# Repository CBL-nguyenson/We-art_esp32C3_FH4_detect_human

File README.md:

# Arduino_Project_Template
      WiFi.begin(network.wifiData.ssid,network.wifiData.pwd);  
      network.wifiData.ssid 
      192.168.4.1

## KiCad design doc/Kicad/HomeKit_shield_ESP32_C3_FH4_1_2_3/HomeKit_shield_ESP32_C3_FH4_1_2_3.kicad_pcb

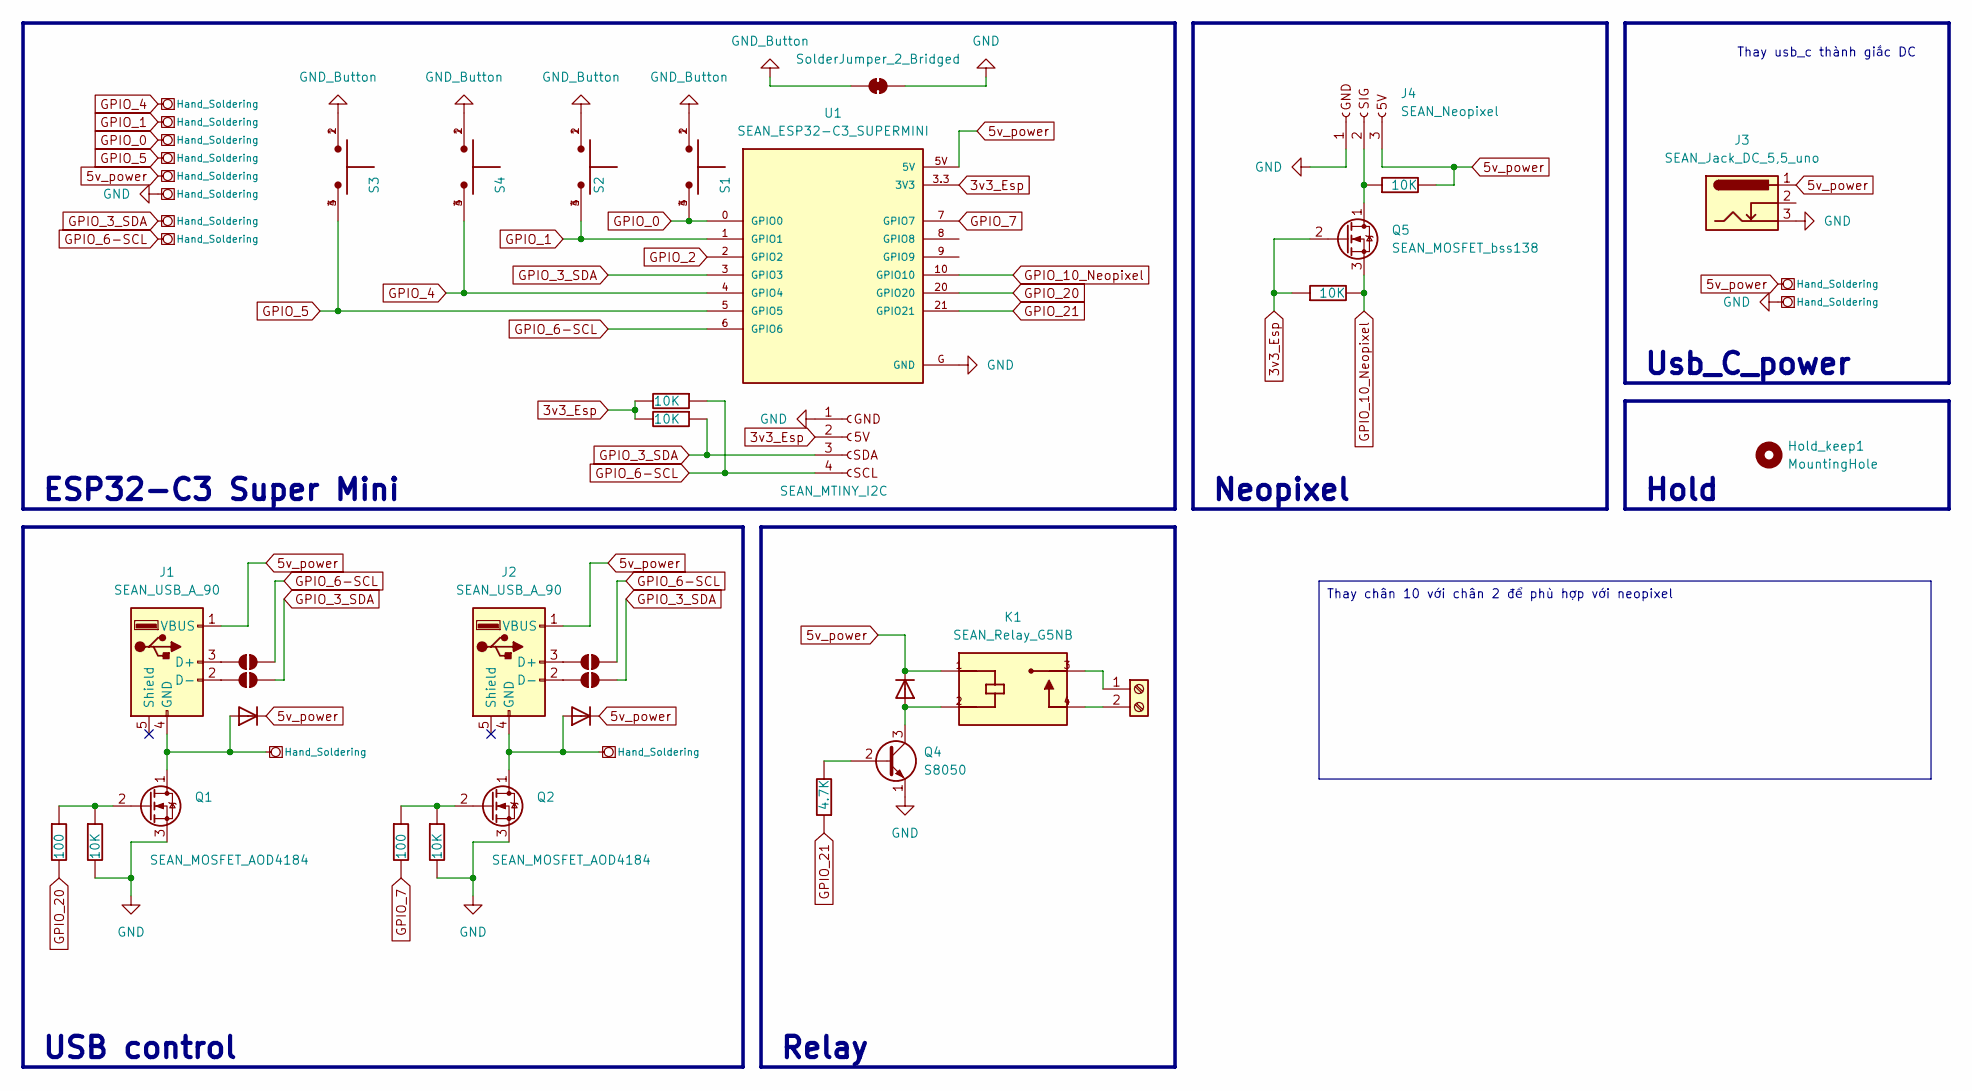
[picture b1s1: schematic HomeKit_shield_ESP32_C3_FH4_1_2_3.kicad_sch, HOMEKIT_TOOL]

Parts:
D1, D2, D3: SEAN_D; SEAN_Diode_1N4007
Hold_keep1: MountingHole; SEAN_MountingHole_3mm_isolated
J1, J2: SEAN_USB_A_90
J3: SEAN_Jack_DC_5,5_uno; SEAN_Jack_DC_5,5_uno_
J4: SEAN_Neopixel
J5: SEAN_MTINY_I2C; SEAN_Mtiny_I2C
JP1, JP2, JP3, JP4: SolderJumper_2_Open; SolderJumper-2_P1.3mm_Open_TrianglePad1.0x1.5mm
JP5: SolderJumper_2_Bridged; SolderJumper-2_P1.3mm_Bridged_RoundedPad1.0x1.5mm
K1: SEAN_Relay_G5NB; SEAN_RELAY_HF46F; PARTREV 1.00
Q1, Q2: SEAN_MOSFET_AOD4184
Q4: S8050; SOT-23-3
Q5: SEAN_MOSFET_bss138
R1, R2, R6, R7, R9, R11: 10K; R_0603_1608Metric_Pad0.98x0.95mm_HandSolder
R3: 4.7K; R_0603_1608Metric_Pad0.98x0.95mm_HandSolder
R4, R5: 100; R_0603_1608Metric_Pad0.98x0.95mm_HandSolder
S1, S2, S3, S4: SEAN_Button_4.2x3.3_SMD_V1
SEAN_Mtiny_Terminal_3.81: SEAN_Mtiny_Terminal_3.81
U1: SEAN_ESP32-C3_SUPERMINI
U2, U3, U4, U5, U6, U7, U8, U9, U10, U11, U12, U13: SEAN_Hand_Solderring

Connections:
3v3_Esp: J5.2 (5V), Q5.2 (G), R6.1, R7.2, R11.2, U1.3.3 (3V3)
5v_power: D1.1 (K), D2.1 (K), D3.1 (K), J1.1 (VBUS), J2.1 (VBUS), J3.1, J4.3 (SDA), K1.1, R9.2, U1.5V, U3.1 (Hand_Soldering), U5.1 (Hand_Soldering)
GND: J3.3, J4.1 (GND), J5.1 (GND), JP5.2 (B), Q1.3 (S), Q2.3 (S), Q4.1 (E), R1.2, R2.2, U1.G (GND), U8.1 (Hand_Soldering), U13.1 (Hand_Soldering)
GND_Button: JP5.1 (A), S1.1, S1.2, S2.1, S2.2, S3.1, S3.2, S4.1, S4.2
GPIO_0: S1.3, S1.4, U1.0 (GPIO0), U6.1 (Hand_Soldering)
GPIO_1: S2.3, S2.4, U1.1 (GPIO1), U7.1 (Hand_Soldering)
GPIO_2: U1.2 (GPIO2)
GPIO_3_SDA: J5.3 (SDA), JP2.2 (B), JP3.2 (B), R7.1, U1.3 (GPIO3), U11.1 (Hand_Soldering)
GPIO_4: S4.3, S4.4, U1.4 (GPIO4), U2.1 (Hand_Soldering)
GPIO_5: S3.3, S3.4, U1.5 (GPIO5), U4.1 (Hand_Soldering)
GPIO_6-SCL: J5.4 (SCL), JP1.2 (B), JP4.2 (B), R11.1, U1.6 (GPIO6), U12.1 (Hand_Soldering)
GPIO_7: R5.2, U1.7 (GPIO7)
GPIO_10_Neopixel: Q5.3 (S), R6.2, U1.10 (GPIO10)
GPIO_20: R4.2, U1.20 (GPIO20)
GPIO_21: R3.1, U1.21 (GPIO21)
unnamed: D1.2 (A), J1.4 (GND), Q1.1 (D), U10.1 (Hand_Soldering)
unnamed: D2.2 (A), J2.4 (GND), Q2.1 (D), U9.1 (Hand_Soldering)
unnamed: D3.2 (A), K1.2, Q4.3 (C)
unnamed: J1.3 (D+), JP4.1 (A)
unnamed: J1.2 (D-), JP3.1 (A)
unnamed: J2.3 (D+), JP1.1 (A)
unnamed: J2.2 (D-), JP2.1 (A)
unnamed: J4.2 (5V), Q5.1 (D), R9.1
unnamed: Q1.2 (G), R1.1, R4.1
unnamed: Q2.2 (G), R2.1, R5.1
unnamed: Q4.2 (B), R3.2
unnamed: K1.3, SEAN_Mtiny_Terminal_3.81.1
unnamed: K1.4, SEAN_Mtiny_Terminal_3.81.2

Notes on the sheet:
Thay chân 10 với chân 2 để phù hợp với neopixel
Relay
ESP32-C3 Super Mini
Thay usb_c thành giắc DC
Hold
Usb_C_power
Neopixel
USB control

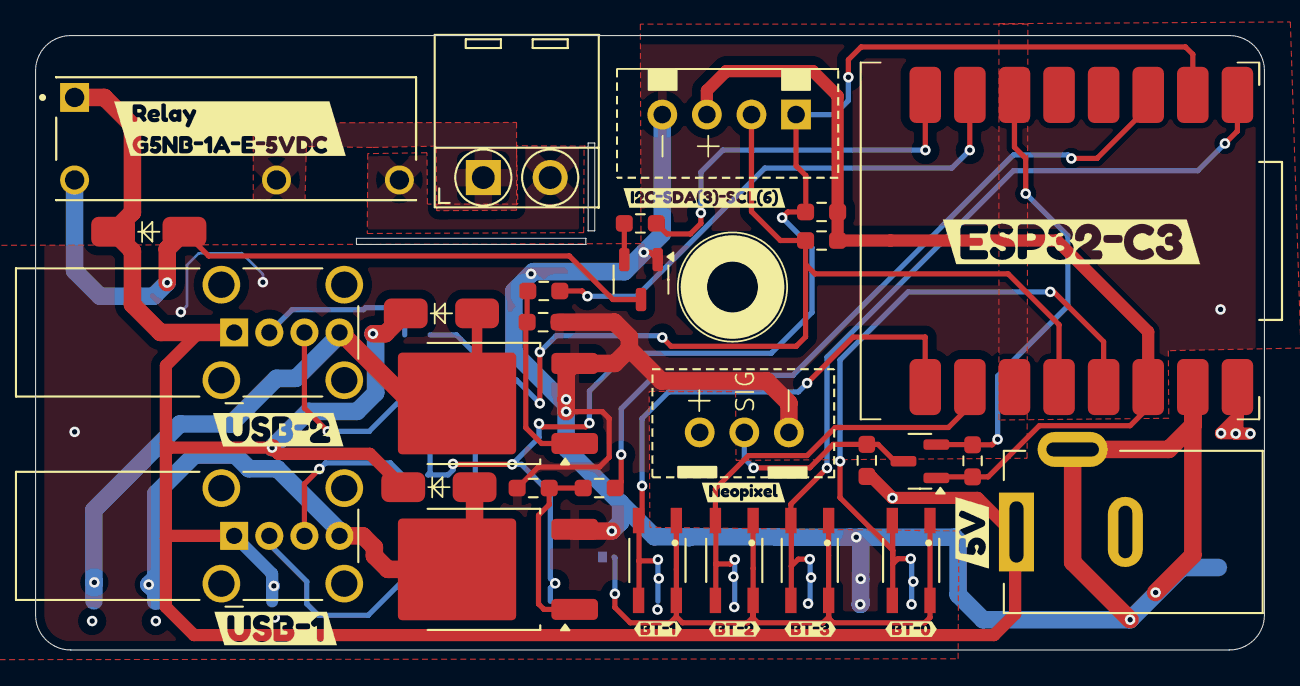
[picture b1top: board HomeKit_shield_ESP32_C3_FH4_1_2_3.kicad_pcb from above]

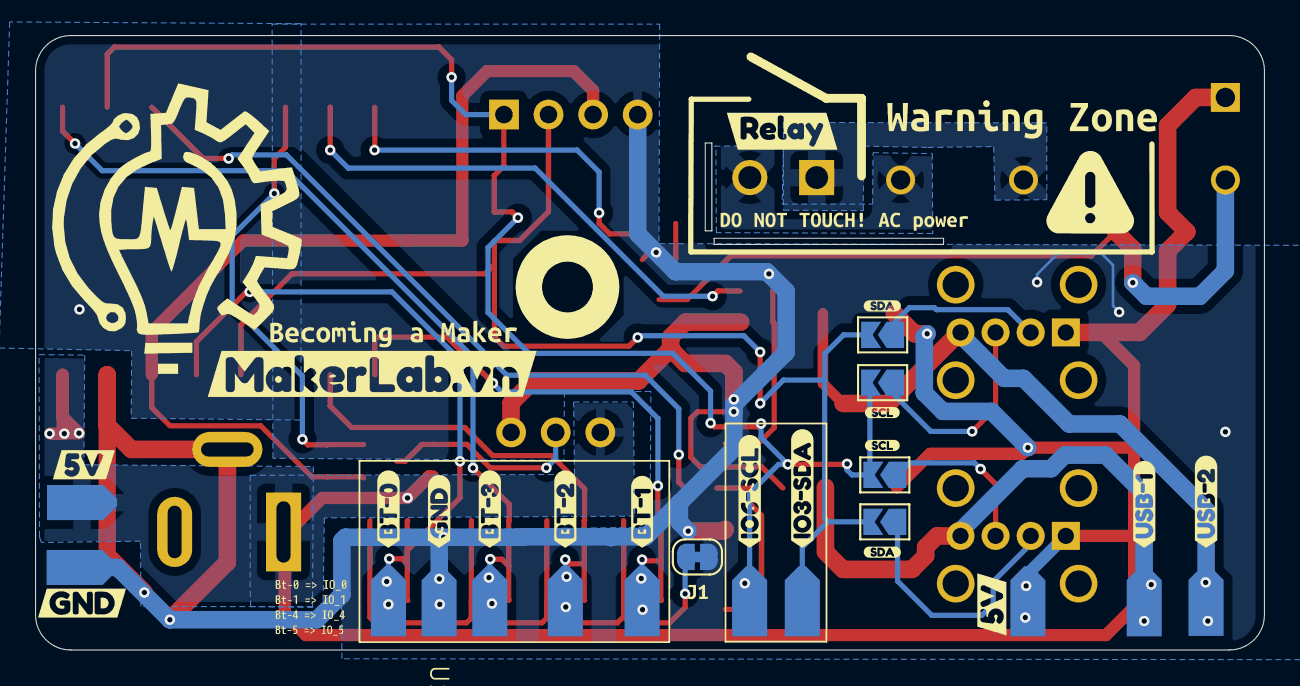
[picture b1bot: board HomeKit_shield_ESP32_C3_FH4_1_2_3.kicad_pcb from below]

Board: 2 copper layers, 70.0 x 35.0 mm, 80 parts (40 on the bottom side), 27 nets.

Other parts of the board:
kibuzzard-66915A6A: G***; kibuzzard-66915A6A
kibuzzard-66915A63: G***; kibuzzard-66915A63
kibuzzard-66915A71: G***; kibuzzard-66915A71
kibuzzard-66915B67: G***; kibuzzard-66915B67
kibuzzard-66915B77: G***; kibuzzard-66915B77
kibuzzard-66915BCA: G***; kibuzzard-66915BCA
kibuzzard-66915BD3: G***; kibuzzard-66915BD3
kibuzzard-66915CB6: G***; kibuzzard-66915CB6
kibuzzard-66915CF0: G***; kibuzzard-66915CF0
kibuzzard-66916D4E: G***; kibuzzard-66916D4E
kibuzzard-66916DF7: G***; kibuzzard-66916DF7
kibuzzard-66916E00: G***; kibuzzard-66916E00
kibuzzard-66916E83: G***; kibuzzard-66916E83
kibuzzard-66916FF3: G***; kibuzzard-66916FF3
kibuzzard-66920A01: G***; kibuzzard-66920A01
kibuzzard-66935D98, kibuzzard-66935D98#2: G***; kibuzzard-66935D98
kibuzzard-66935DA9, kibuzzard-66935DA9#2: G***; kibuzzard-66935DA9
kibuzzard-66935E99: G***; kibuzzard-66935E99
kibuzzard-66938FC6: G***; kibuzzard-66938FC6
kibuzzard-66940ABD: G***; kibuzzard-66940ABD
kibuzzard-66940BD0: G***; kibuzzard-66940BD0
kibuzzard-66940CA3: G***; kibuzzard-66940CA3
kibuzzard-669170D7: G***; kibuzzard-669170D7
kibuzzard-669170EF: G***; kibuzzard-669170EF
kibuzzard-669170F7: G***; kibuzzard-669170F7
kibuzzard-669206A7: G***; kibuzzard-669206A7
kibuzzard-669409A1: G***; kibuzzard-669409A1
kibuzzard-6691741D: G***; kibuzzard-6691741D
kibuzzard-66917101: G***; kibuzzard-66917101
kibuzzard-66917287: G***; kibuzzard-66917287
kibuzzard-66917505: G***; kibuzzard-66917505
kibuzzard-66920690: G***; kibuzzard-66920690

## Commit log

2024-05-05 test
2024-05-08 save
2024-05-10 Homespan
2024-05-10 Send-sensor
2024-05-11 quá mệt mỏi
2024-05-15 Detect_human_homespan chạy oke
2024-05-17 Da chay
2024-05-24 Fan Set okeeee
2024-05-24 bi khung rui
2024-05-25 Okeee đã chạy
2024-05-25 Run Yeeeeeeeeeeeee
2024-05-26 Change
2024-05-26 Manager files
2024-05-26 Update LICENSE
2024-05-26 y24m05d26: Learn Wifi_AP_mode
2024-05-28 Quá đau khổ
2024-05-28 network
2024-05-28 28/5 bị khùng phần string
2024-05-28 28/5 ngu thui
2024-05-29 Picture
2024-05-30 Network_run
2024-05-30 Network_html
2024-06-07 Kicad
2024-06-26 Pixel
2024-07-18 auto AP Wifi
